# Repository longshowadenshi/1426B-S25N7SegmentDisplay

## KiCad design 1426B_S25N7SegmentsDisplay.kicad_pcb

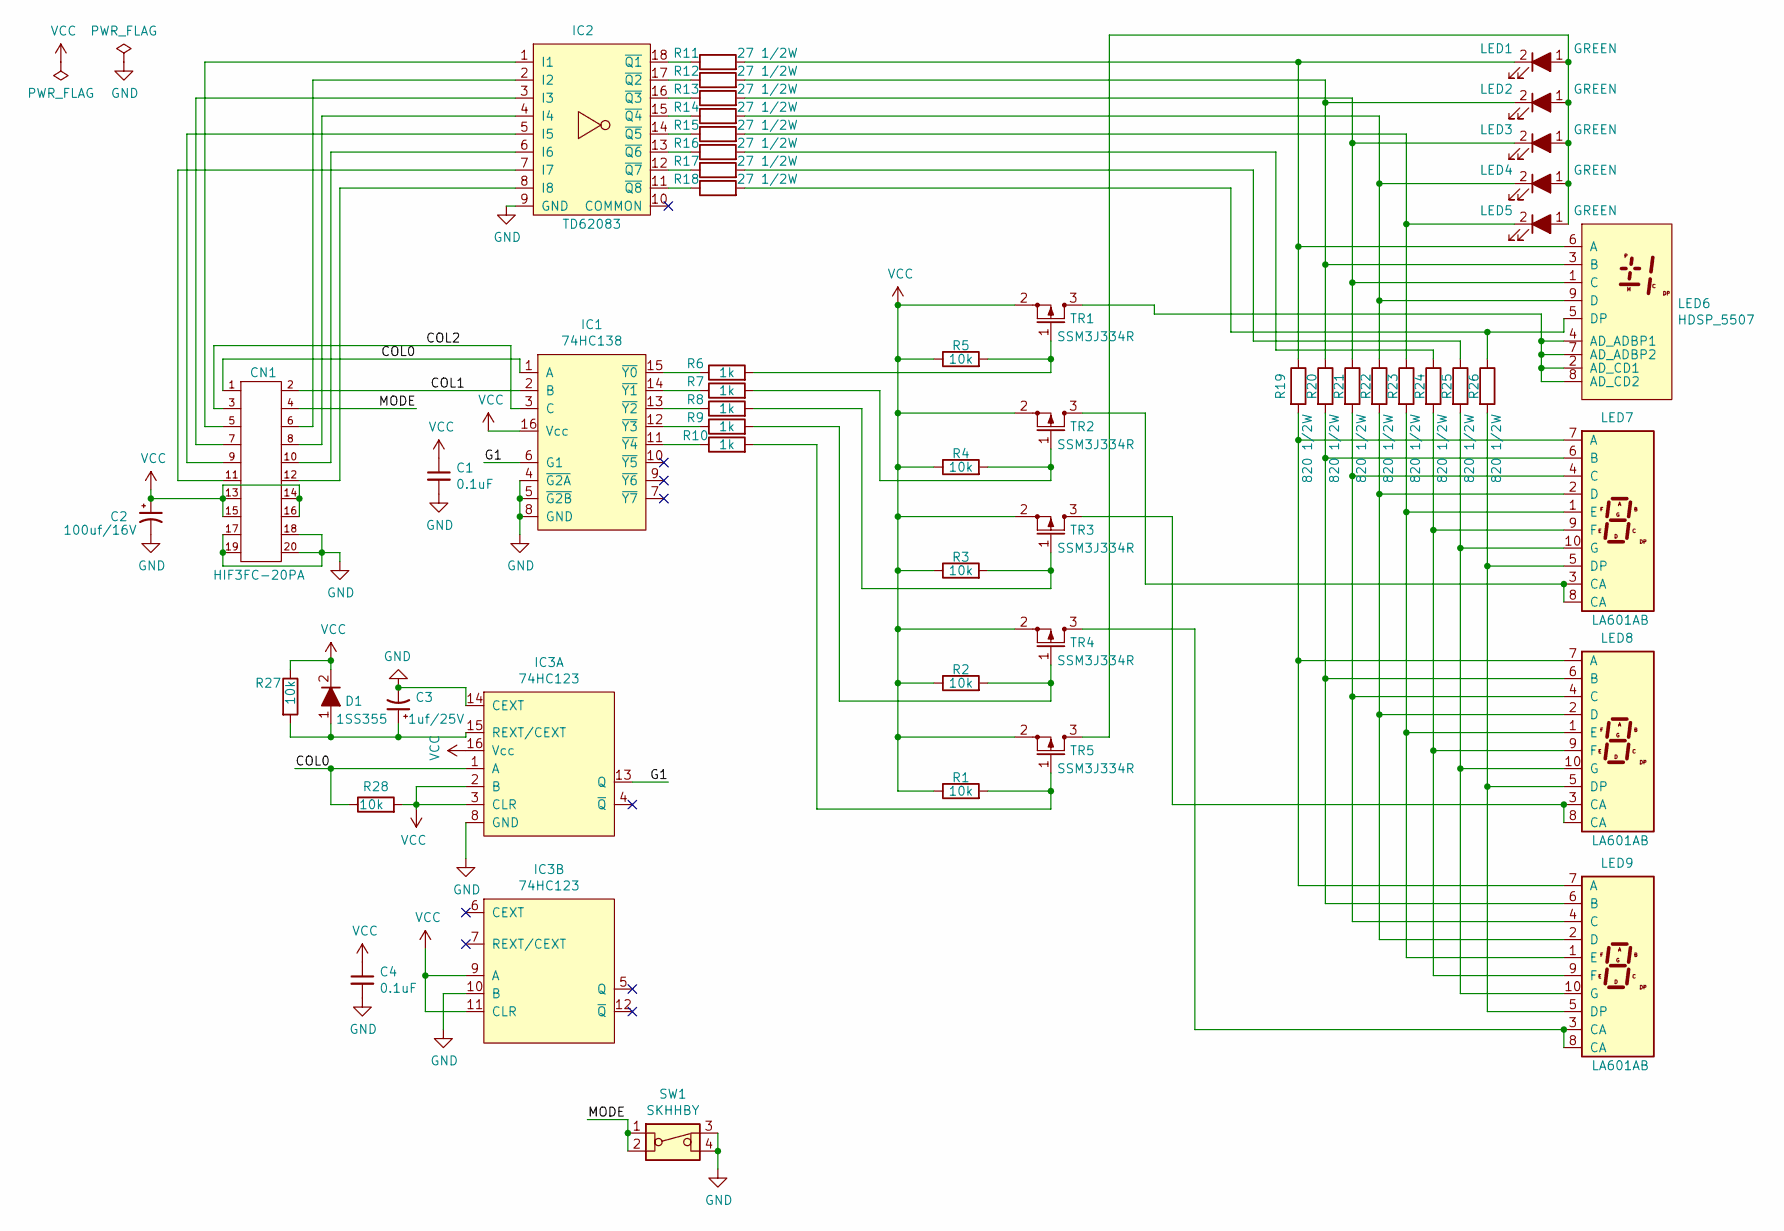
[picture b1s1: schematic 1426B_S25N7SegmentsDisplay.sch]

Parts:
C1, C4: 0.1uF; C0603C104Z3VACTU
C2: 100uf/16V; 10uF-16v
C3: 1uf/25V; 10uF-16v
CN1: HIF3FC-20PA; HIF3FC-20PA-2.54DSA
D1: 1SS355
IC1: 74HC138; 74HC161AP
IC2: TD62083
IC3: 74HC123; 74HC161AP
LED1, LED2, LED3, LED4, LED5: GREEN; led_sq
LED6: HDSP_5507; HDSP5307
LED7, LED8, LED9: LA601AB
R1, R2, R3, R4, R5, R27, R28: 10k; C1608C0G1H682J
R6, R7, R8, R9, R10: 1k; C1608C0G1H682J
R11, R12, R13, R14, R15, R16, R17, R18: 27 1/2W; RMCF1210
R19, R20, R21, R22, R23, R24, R25, R26: 820 1/2W; RMCF1210
SW1: SKHHBY
TR1, TR2, TR3, TR4, TR5: SSM3J334R

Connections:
/COL0: CN1.1, IC1.1 (A), IC3.1 (A), R28.1
/COL1: CN1.2, IC1.2 (B)
/COL2: CN1.3, IC1.3 (C)
/G1: IC1.6 (G1), IC3.13 (Q)
/MODE: CN1.4, SW1.1, SW1.2
GND: C1.2, C2.2, C3.2, C4.2, CN1.17, CN1.18, CN1.19, CN1.20, IC1.4 (~G2A), IC1.5 (~G2B), IC1.8 (GND), IC2.9 (GND), IC3.8 (GND), IC3.10 (B), IC3.14 (CEXT), SW1.3, SW1.4
unnamed: C3.1, D1.1, IC3.15 (REXT/CEXT), R27.2
unnamed: CN1.5, IC2.1 (I1)
unnamed: CN1.6, IC2.2 (I2)
unnamed: CN1.7, IC2.3 (I3)
unnamed: CN1.8, IC2.4 (I4)
unnamed: CN1.9, IC2.5 (I5)
unnamed: CN1.10, IC2.6 (I6)
unnamed: CN1.11, IC2.7 (I7)
unnamed: CN1.12, IC2.8 (I8)
unnamed: IC1.11 (~Y4), R10.1
unnamed: IC1.12 (~Y3), R9.1
unnamed: IC1.13 (~Y2), R8.1
unnamed: IC1.14 (~Y1), R7.1
unnamed: IC1.15 (~Y0), R6.1
unnamed: IC2.11 (~Q8), R18.1
unnamed: IC2.12 (~Q7), R17.1
unnamed: IC2.13 (~Q6), R16.1
unnamed: IC2.14 (~Q5), R15.1
unnamed: IC2.15 (~Q4), R14.1
unnamed: IC2.16 (~Q3), R13.1
unnamed: IC2.17 (~Q2), R12.1
unnamed: IC2.18 (~Q1), R11.1
unnamed: LED1.1, LED2.1, LED3.1, LED4.1, LED5.1, TR5.3
unnamed: LED1.2, LED6.6 (A), R11.2, R19.1
unnamed: LED2.2, LED6.3 (B), R12.2, R20.1
unnamed: LED3.2, LED6.1 (C), R13.2, R21.1
unnamed: LED4.2, LED6.9 (D), R14.2, R22.1
unnamed: LED5.2, R15.2, R23.1
unnamed: LED6.2 (AD_CD1), LED6.4 (AD_ADBP1), LED6.7 (AD_ADBP2), LED6.8 (AD_CD2), TR1.3
unnamed: LED6.5 (DP), R18.2, R26.1
unnamed: LED7.1 (E), LED8.1 (E), LED9.1 (E), R23.2
unnamed: LED7.2 (D), LED8.2 (D), LED9.2 (D), R22.2
unnamed: LED7.3 (CA), LED7.8 (CA), TR2.3
unnamed: LED7.4 (C), LED8.4 (C), LED9.4 (C), R21.2
unnamed: LED7.5 (DP), LED8.5 (DP), LED9.5 (DP), R26.2
unnamed: LED7.6 (B), LED8.6 (B), LED9.6 (B), R20.2
unnamed: LED7.7 (A), LED8.7 (A), LED9.7 (A), R19.2
unnamed: LED7.9 (F), LED8.9 (F), LED9.9 (F), R24.2
unnamed: LED7.10 (G), LED8.10 (G), LED9.10 (G), R25.2
unnamed: LED8.3 (CA), LED8.8 (CA), TR3.3
unnamed: LED9.3 (CA), LED9.8 (CA), TR4.3
unnamed: R1.2, R10.2, TR5.1
unnamed: R2.2, R9.2, TR4.1
unnamed: R3.2, R8.2, TR3.1
unnamed: R4.2, R7.2, TR2.1
unnamed: R5.2, R6.2, TR1.1
unnamed: R16.2, R24.1
unnamed: R17.2, R25.1
VCC: C1.1, C2.1, C4.1, CN1.13, CN1.14, CN1.15, CN1.16, D1.2, IC1.16 (Vcc), IC3.2 (B), IC3.3 (CLR), IC3.9 (A), IC3.11 (CLR), IC3.16 (Vcc), R1.1, R2.1, R3.1, R4.1, R5.1, R27.1, R28.2, TR1.2, TR2.2, TR3.2, TR4.2, TR5.2

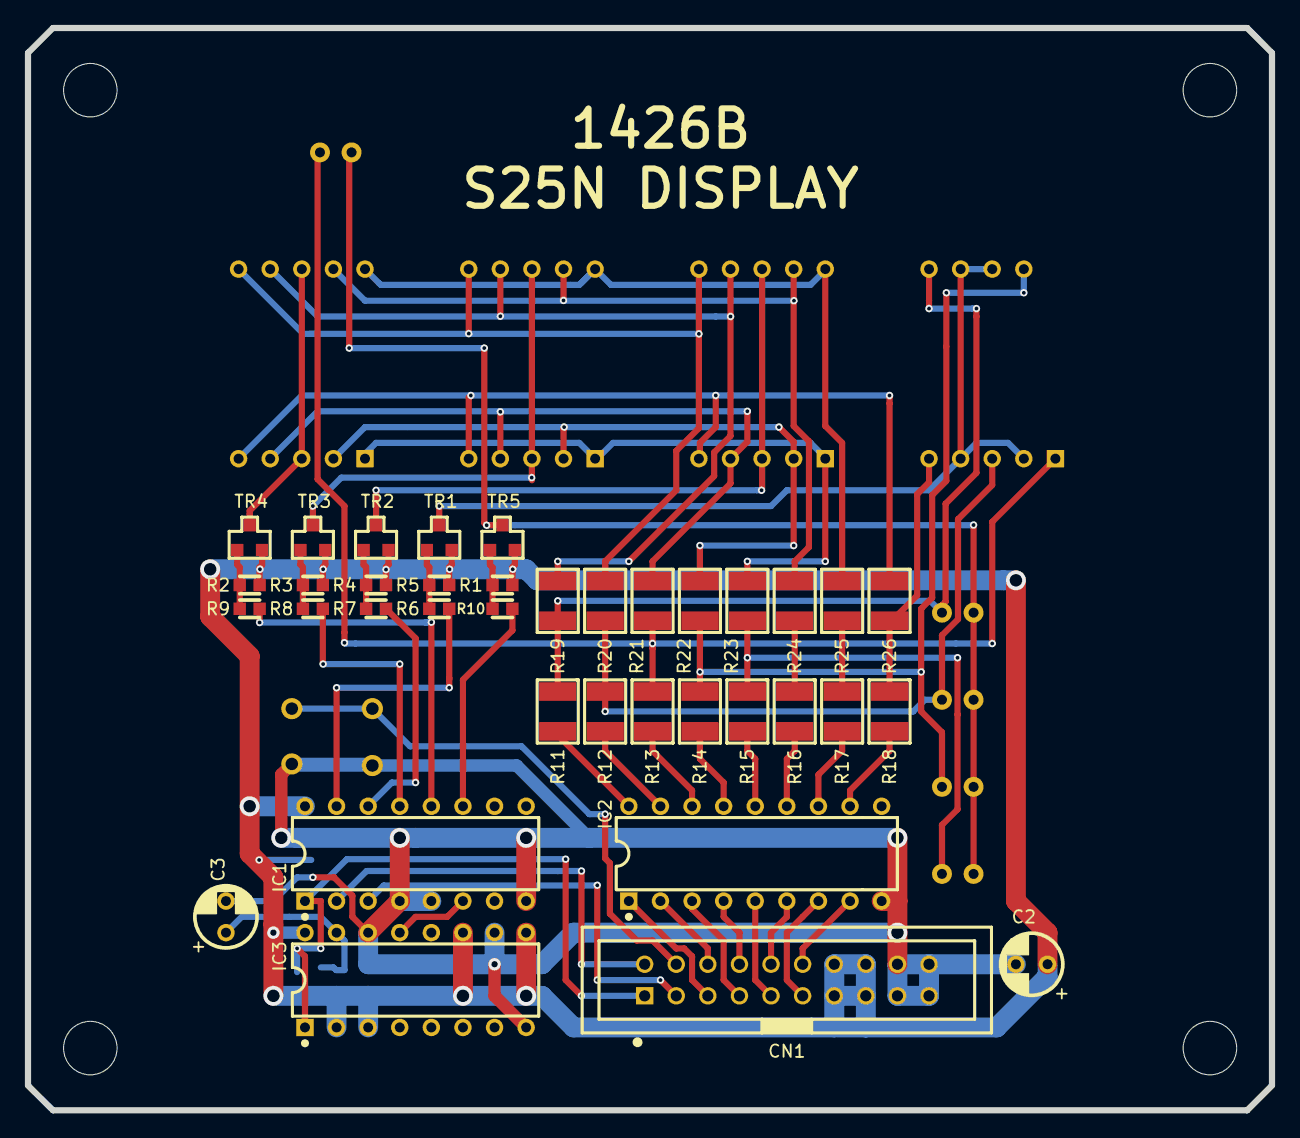
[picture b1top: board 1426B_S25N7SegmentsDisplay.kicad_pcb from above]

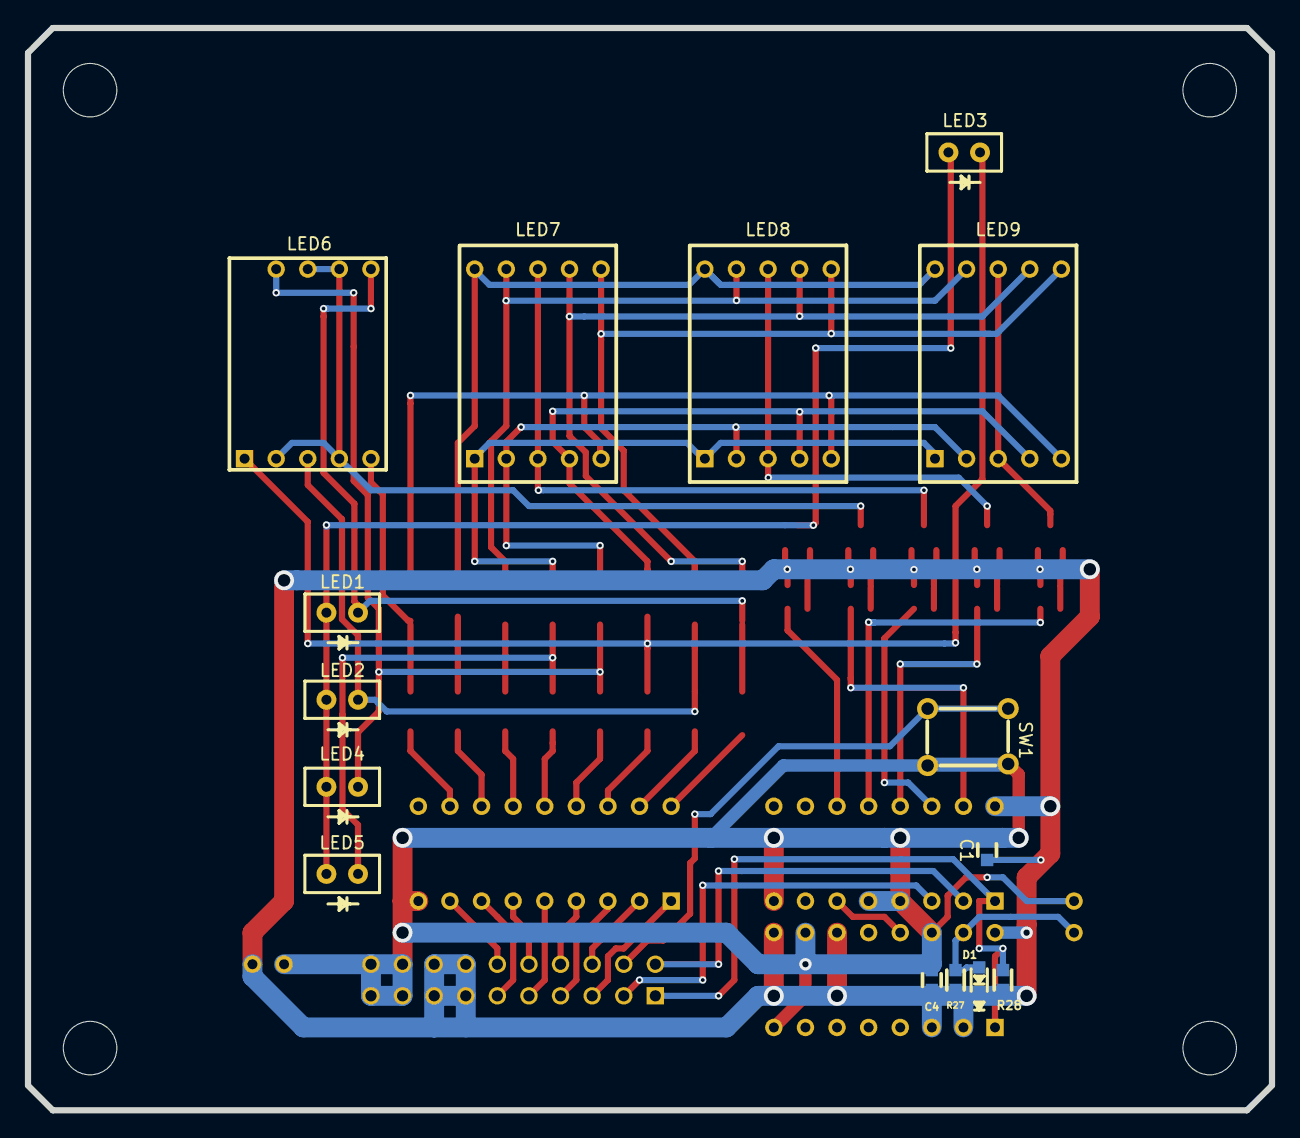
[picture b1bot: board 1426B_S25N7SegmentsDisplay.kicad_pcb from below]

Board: 2 copper layers, 100.0 x 87.0 mm, 52 parts (15 on the bottom side), 55 nets.
